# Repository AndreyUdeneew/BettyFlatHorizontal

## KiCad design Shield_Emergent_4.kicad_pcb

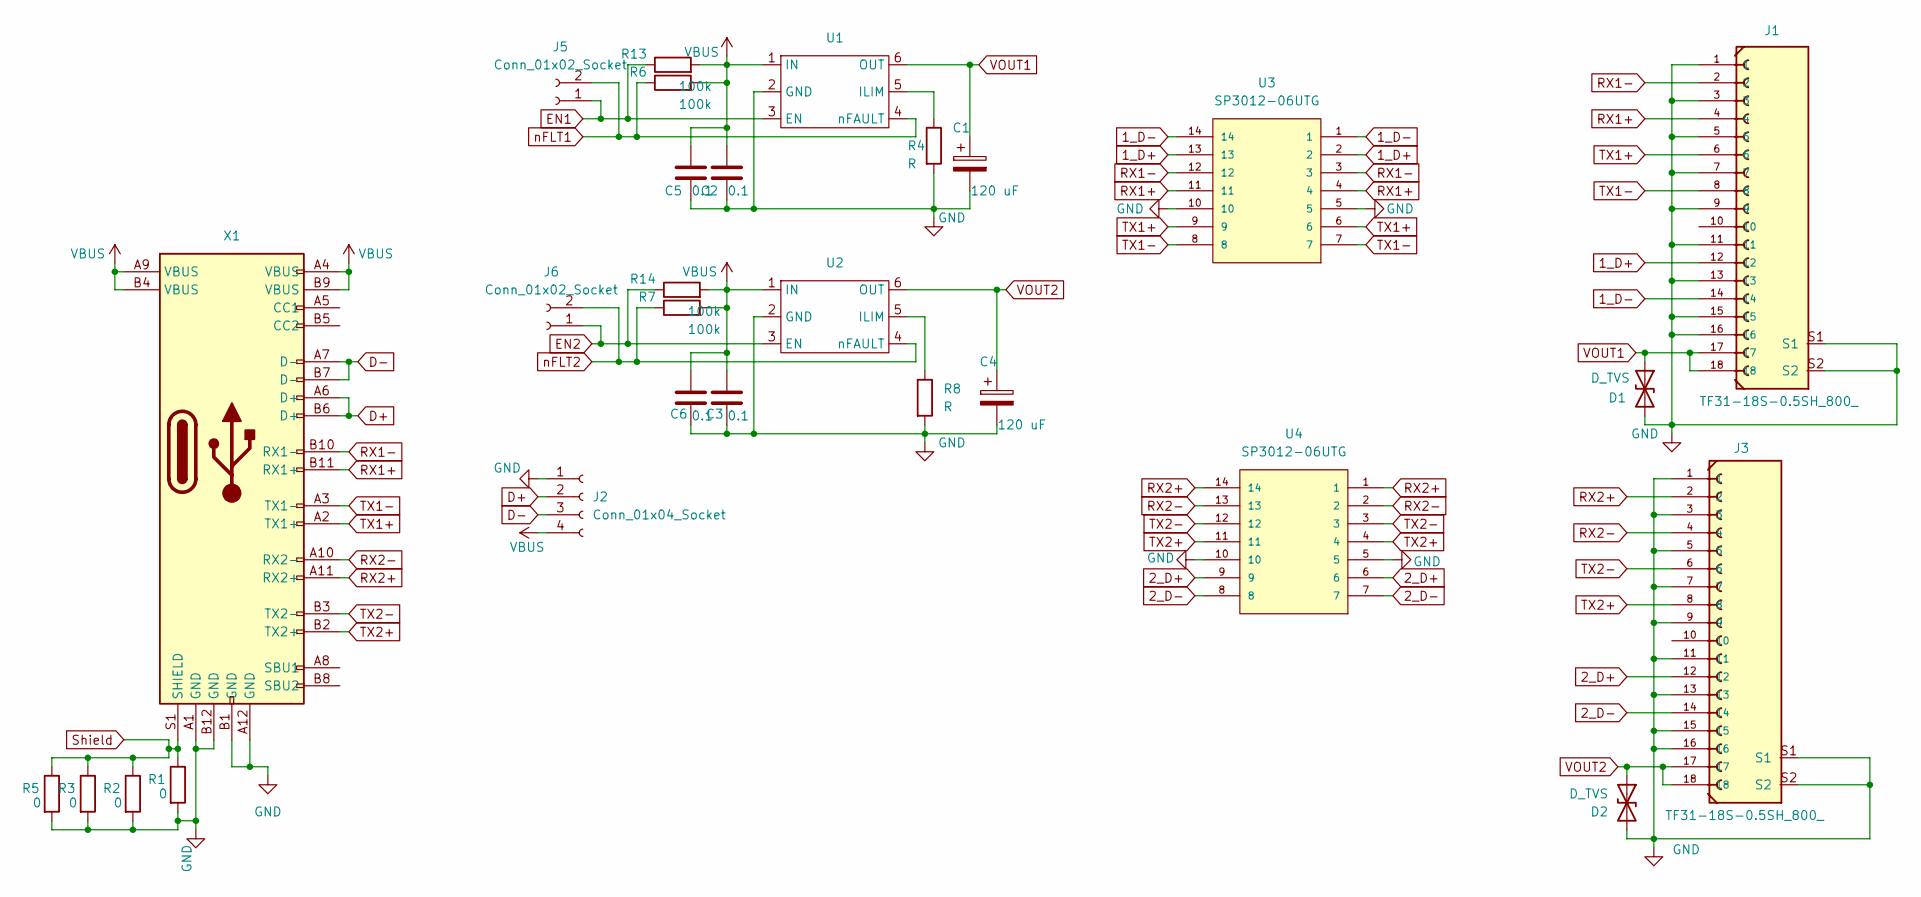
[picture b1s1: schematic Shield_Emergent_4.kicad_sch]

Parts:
C1, C4: 120 uF; CP_Radial_D5.0mm_P2.00mm
C2, C3, C5, C6: 0.1; C_0402_1005Metric_Pad0.74x0.62mm_HandSolder
D1, D2: D_TVS; D_SOD-523
J1, J3: TF31-18S-0.5SH_800_; HRS_TF31-18S-0.5SH_800_
J2: Conn_01x04_Socket; PinSocket_1x04_P2.54mm_Vertical
J5, J6: Conn_01x02_Socket; PinHeader_1x02_P1.27mm_Vertical
R1, R2, R3, R5: 0; R_0201_0603Metric_Pad0.64x0.40mm_HandSolder
R4, R8: R; R_0402_1005Metric_Pad0.72x0.64mm_HandSolder
R6, R7, R13, R14: 100k; R_0402_1005Metric_Pad0.72x0.64mm_HandSolder
U1, U2: SOT-23-6_Handsoldering
U3, U4: SP3012-06UTG; DFN-14_1.35x3.5mm_P0.5mm; PARTREV 02/23/17
X1: USB_C_24pins; USB_C_Receptacle_JAE_DX07S024WJ3R400

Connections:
1_D+: J1.12, U3.2, U3.13
1_D-: J1.14, U3.1, U3.14
2_D+: J3.12, U4.6, U4.9
2_D-: J3.14, U4.7, U4.8
D+: J2.2, X1.A6 (D+), X1.B6 (D+)
D-: J2.3, X1.A7 (D-), X1.B7 (D-)
EN1: J5.1, R13.1, U1.3 (EN)
EN2: J6.1, R14.1, U2.3 (EN)
GND: C1.2, C2.2, C3.2, C4.2, C5.2, C6.2, D1.2 (A2), D2.2 (A2), J1.1, J1.3, J1.5, J1.7, J1.9, J1.11, J1.13, J1.15, J1.16, J1.S1, J1.S2, J2.1, J3.1, J3.3, J3.5, J3.7, J3.9, J3.11, J3.13, J3.15, J3.16, J3.S1, J3.S2, R1.2, R2.2, R3.2, R4.2, R5.2, R8.2, U1.2 (GND), U2.2 (GND), U3.5, U3.10, U4.5, U4.10, X1.A1 (GND), X1.A12 (GND), X1.B1 (GND), X1.B12 (GND)
unnamed: R4.1, U1.5 (ILIM)
unnamed: R8.1, U2.5 (ILIM)
RX1+: J1.4, U3.4, U3.11, X1.B11 (RX1+)
RX1-: J1.2, U3.3, U3.12, X1.B10 (RX1-)
RX2+: J3.2, U4.1, U4.14, X1.A11 (RX2+)
RX2-: J3.4, U4.2, U4.13, X1.A10 (RX2-)
Shield: R1.1, R2.1, R3.1, R5.1, X1.S1 (SHIELD), X1.S2 (SHIELD), X1.S3 (SHIELD), X1.S4 (SHIELD)
TX1+: J1.6, U3.6, U3.9, X1.A2 (TX1+)
TX1-: J1.8, U3.7, U3.8, X1.A3 (TX1-)
TX2+: J3.8, U4.4, U4.11, X1.B2 (TX2+)
TX2-: J3.6, U4.3, U4.12, X1.B3 (TX2-)
VBUS: C2.1, C3.1, C5.1, C6.1, J2.4, R6.2, R7.2, R13.2, R14.2, U1.1 (IN), U2.1 (IN), X1.A4 (VBUS), X1.A9 (VBUS), X1.B4 (VBUS), X1.B9 (VBUS)
VOUT1: C1.1, D1.1 (A1), J1.17, J1.18, U1.6 (OUT)
VOUT2: C4.1, D2.1 (A1), J3.17, J3.18, U2.6 (OUT)
nFLT1: J5.2, R6.1, U1.4 (nFAULT)
nFLT2: J6.2, R7.1, U2.4 (nFAULT)

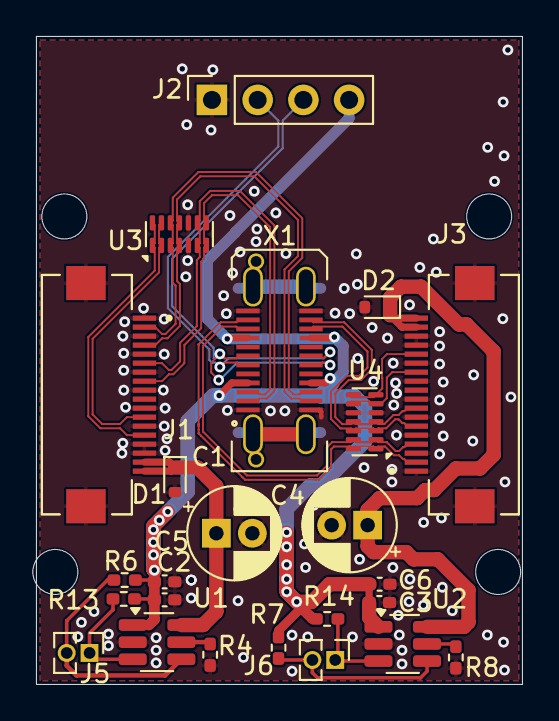
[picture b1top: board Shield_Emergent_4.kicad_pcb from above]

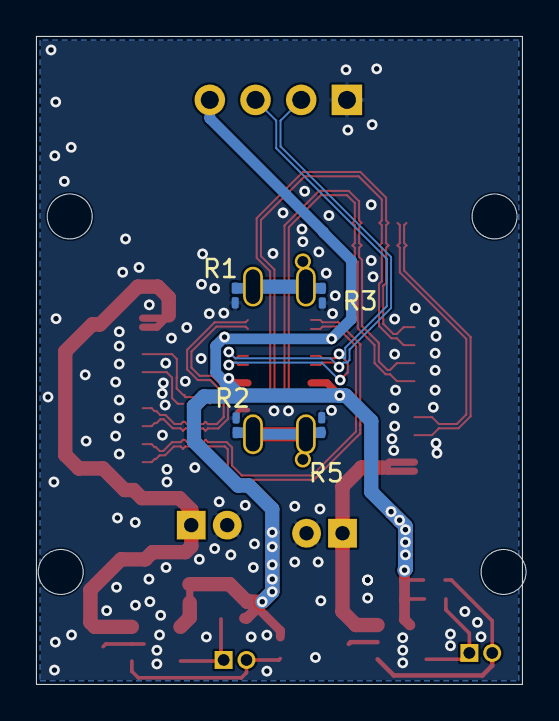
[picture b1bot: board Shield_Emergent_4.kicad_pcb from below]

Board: 4 copper layers, 27.0 x 36.0 mm, 28 parts (4 on the bottom side), 25 nets.

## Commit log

2025-03-14 v0.1 draft routing
2025-03-14 v0.2 silkscreen was corrected, DRC was completed
